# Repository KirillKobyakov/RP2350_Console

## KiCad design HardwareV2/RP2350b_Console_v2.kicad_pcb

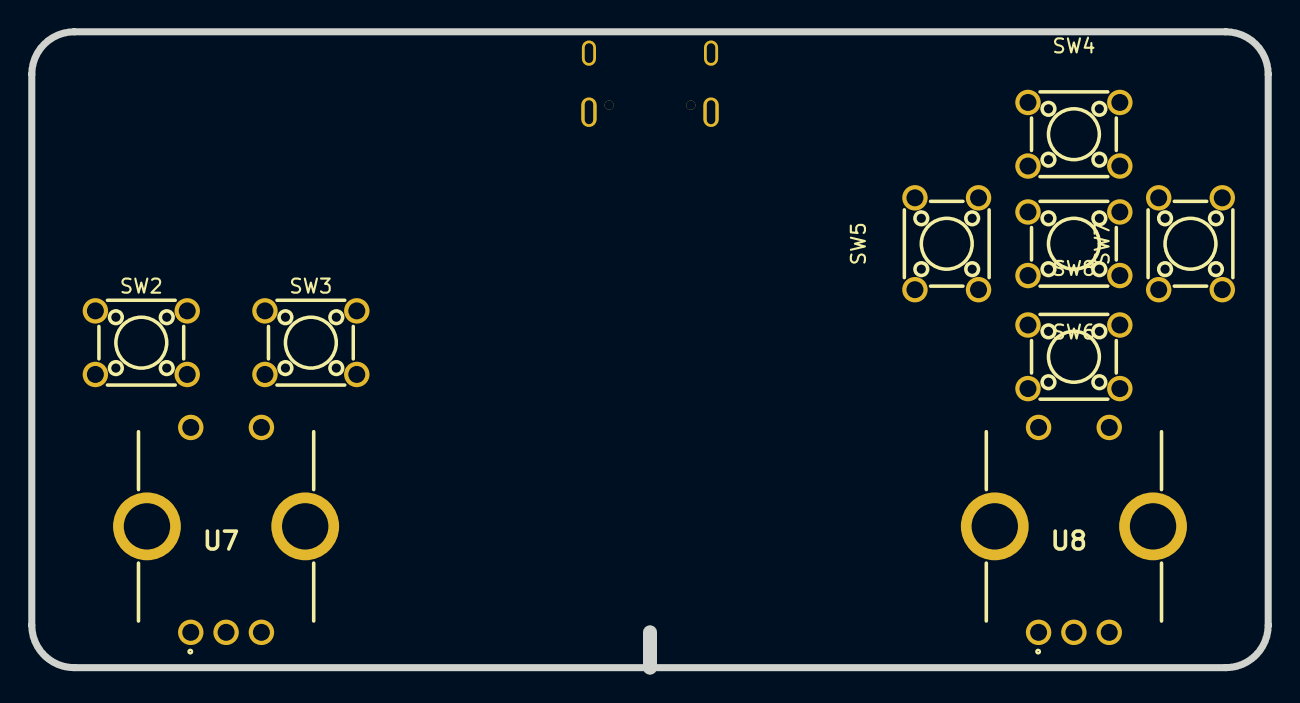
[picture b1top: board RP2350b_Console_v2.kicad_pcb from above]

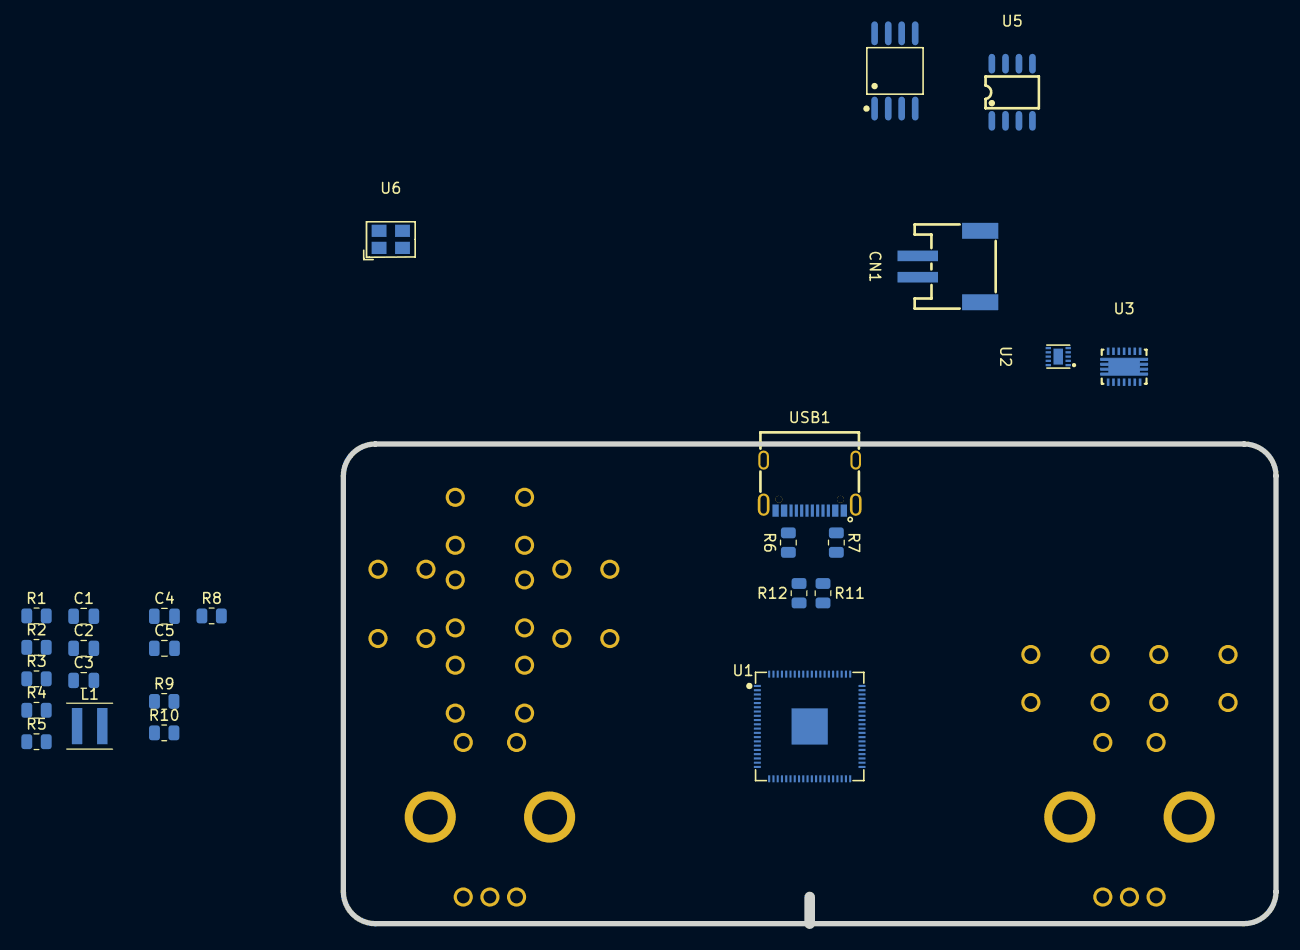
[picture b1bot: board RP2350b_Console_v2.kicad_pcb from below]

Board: 4 copper layers, 87.5 x 45.0 mm, 35 parts (26 on the bottom side), 26 nets, no tracks yet.

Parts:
C1: 47u; C_0805_2012Metric
C2: 22u; C_0805_2012Metric
C3: 100n; C_0805_2012Metric
C4, C5: 15p; C_0805_2012Metric
CN1: S2B-PH-SM4-TB(LF)(SN); CONN-SMD_P2.00_S2B-PH-SM4-TB-LF-SN
L1: 1.5u; L_Coilcraft_XxL4020
R1: 2k; R_0805_2012Metric
R2: 540; R_0805_2012Metric
R3: 10k; R_0805_2012Metric
R4, R5: R; R_0805_2012Metric
R6, R7: 5.1k; R_0805_2012Metric
R8, R9, R10: 1k; R_0805_2012Metric
R11, R12: 27; R_0805_2012Metric
SW2, SW3, SW4, SW5, SW6, SW7, SW8: 1825910-6; SW-TH_4P-L6.0-W6.0-P4.50-LS6.5
U1: RP2350B_C42415655; QFN-80_L10.0-W10.0-P0.40-TL-EP3.4
U2: BQ24040DSQR; WSON-10_L2.0-W2.0-P0.40-BL-EP
U3: TPS63021DSJR; VSON-14_L4.0-W3.0-P0.50-BL-EP_TI_DSJ
U4: W25Q128JVSIQTR; SOIC-8_L5.3-W5.3-P1.27-LS8.0-BL
U5: LY68L6400SLIT; SOP-8_L4.9-W3.9-P1.27-LS6.0-BL
U6: ABM8-272-T3; CRYSTAL-SMD_4P-L3.2-W2.5-BL-2
U7, U8: PEC12R-4215F-S0024; PEC12R-4XXXF-SXXXX_1
USB1: USB-310; USB-C-SMD_20P-P0.50-L7.4-W8.9

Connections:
+3V3: C1.1, U3.3 (FB), U3.4 (VOUT), U3.5 (VOUT), U4.8 (VCC), U5.8 (VCC)
+BATT: C2.1, CN1.1, R4.2, R5.2, U2.10 (OUT), U3.10 (VIN), U3.11 (VIN)
GND: C1.2, C2.2, C3.2, C4.2, C5.2, CN1.2, CN1.3, CN1.4, R1.2, R2.2, R3.2, R6.2, R7.2, SW2.3, SW2.4, SW3.3, SW3.4, U2.3 (VSS), U2.7 (ISET2), U2.11 (EP), U3.2 (GND), U3.13 (PS/SYNC), U3.15 (PGND), U4.4 (GND), U5.4 (VSS), U6.2 (GND), U6.4 (GND), USB1.0, USB1.A1 (GND), USB1.A12 (GND), USB1.B1 (GND), USB1.B12 (GND)
unnamed: C4.1, R8.1, U6.3
unnamed: L1.1, U3.8 (L1), U3.9 (L1)
unnamed: L1.2, U3.6 (L2), U3.7 (L2)
unnamed: R9.2, SW2.1, SW2.2
unnamed: R10.2, SW3.1, SW3.2
unnamed: C3.1, U3.1 (VINA)
unnamed: R11.2, U1.66 (USB_DM)
unnamed: R12.2, U1.67 (USB_DP)
unnamed: R2.1, U2.2 (ISET)
unnamed: R1.1, U2.4 (PRETERM)
unnamed: R3.1, U2.9 (TS)
unnamed: R6.1, USB1.A5 (CC1)
unnamed: R7.1, USB1.B5 (CC2)
QSPI_0: U1.72 (QSPI_SD0), U4.5 (DI), U5.5 (SI/SIO[0])
QSPI_1: U1.74 (QSPI_SD1), U4.2 (DO), U5.2 (SO/SIO[1])
QSPI_2: U1.73 (QSPI_SD2), U4.3 (IO2), U5.3 (SIO[2])
QSPI_3: U1.70 (QSPI_SD3), U4.7 (IO3), U5.7 (SIO[3])
QSPI_CLK: U1.71 (QSPI_SCLK), U4.6 (CLK), U5.6 (SCLK)
QSPI_SS0: R9.1, U1.75 (QSPI_SS), U4.1 (~CS)
USB_D+: R12.1, USB1.A6 (D+), USB1.B6 (D+)
USB_D-: R11.1, USB1.A7 (D-), USB1.B7 (D-)
VBUS: U2.1 (IN), USB1.A4 (VBUS), USB1.A9 (VBUS), USB1.B4 (VBUS), USB1.B9 (VBUS)
XIN: C5.1, U6.1

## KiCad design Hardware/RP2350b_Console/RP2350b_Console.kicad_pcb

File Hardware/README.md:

# RP2350_Console
A custom RP2350b console, which will include an LCD screen and rotary quad encoders. In this repository will include both hardware and software components for the design as well as assembly components and a tutorial.

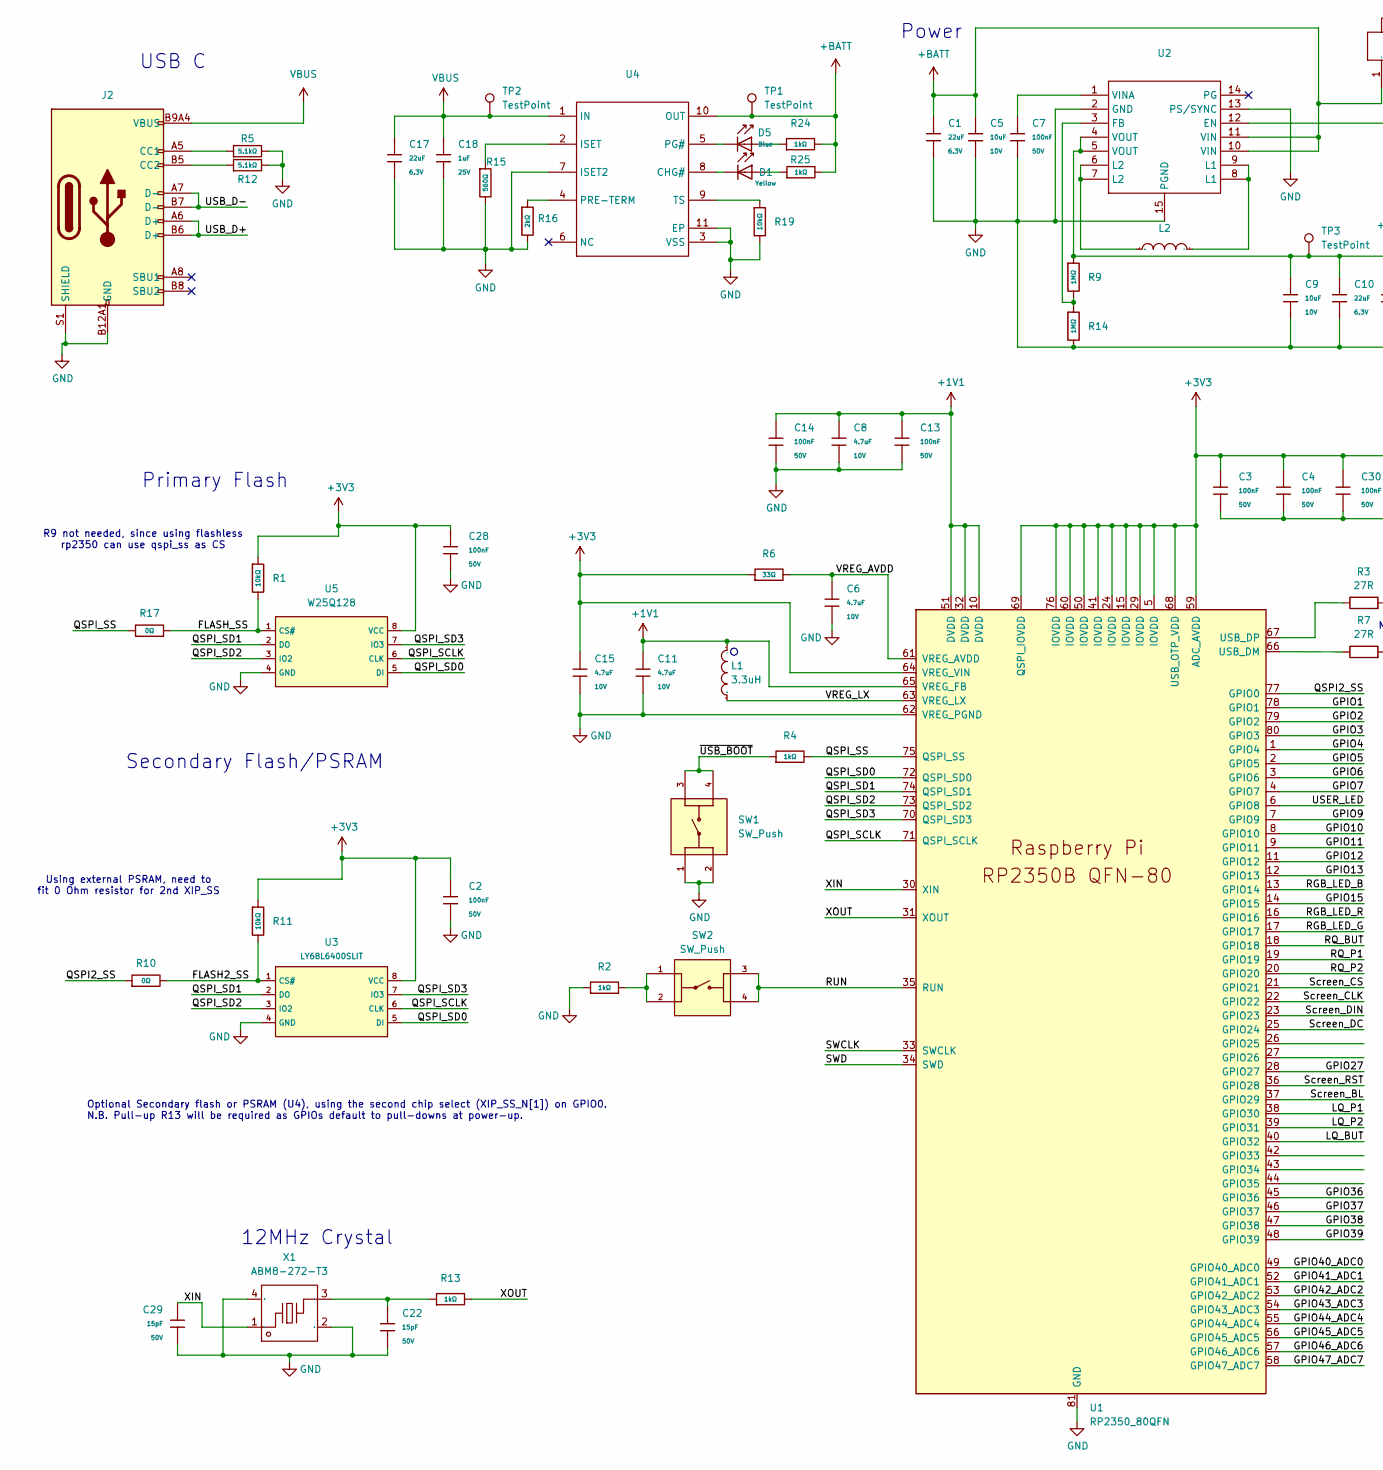
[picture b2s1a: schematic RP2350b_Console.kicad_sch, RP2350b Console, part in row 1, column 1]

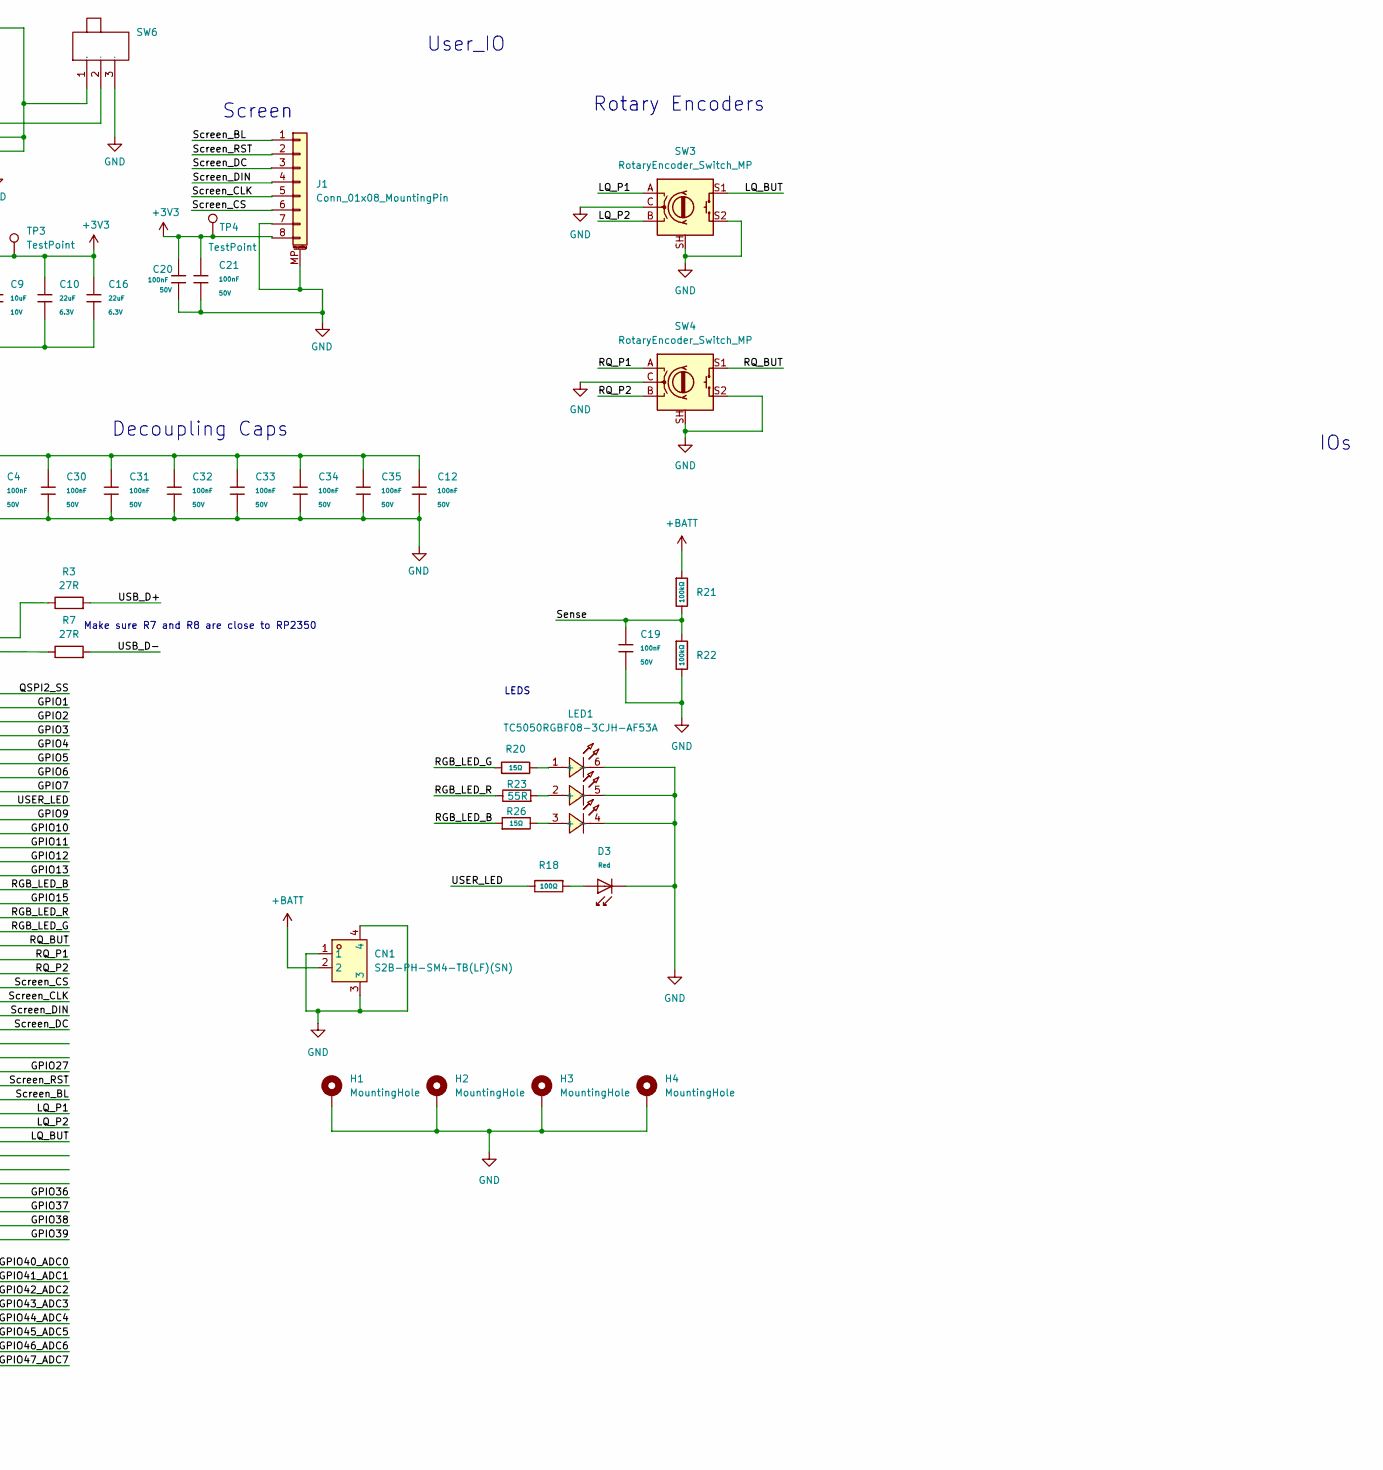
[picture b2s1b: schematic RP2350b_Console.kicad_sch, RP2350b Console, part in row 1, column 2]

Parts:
C1, C10, C16, C17: 22uF; C_0603; Voltage Rated 6.3V; Tolerance ±20%; Part CL10A226MQ8NRNC; LCSC C59461
C2, C3, C4, C7, C12, C13, C14, C19, C20, C21, C28, C30, C31, C32, C33, C34, C35: 100nF; C_0402; Voltage Rated 50V; Tolerance ±10%; Part CL05B104KB54PNC; LCSC C307331
C5, C9: 10uF; C_0603; Voltage Rated 10V; Tolerance ±10%; Part CL10A106KP8NNNC; LCSC C19702
C6, C8, C11, C15: 4.7uF; C_0402; Voltage Rated 10V; Tolerance ±20%; Part CL05A475MP5NRNC; LCSC C23733
C18: 1uF; C_0402; Voltage Rated 25V; Tolerance ±10%; Part CL05A105KA5NQNC; LCSC C52923
C22, C29: 15pF; C_0402; Voltage Rated 50V; Tolerance ±5%; Part 0402CG150J500NT; LCSC C1548
CN1: S2B-PH-SM4-TB(LF)(SN); CONN-SMD_P2.00_S2B-PH-SM4-TB-LF-SN; LCSC Part C295747
D1: Yellow; LED0603-R-RD_AMBER; Part KT-0603R; LCSC C2286
D3: Red; D_0603; Part KT-0603R; LCSC C2286
D5: Blue; LED0603-FD_BLUE; Part KT-0603R; LCSC C2286
H1, H2, H3, H4: MountingHole; MountingHole_2.2mm_M2_Pad_TopBottom
J1: Conn_01x08_MountingPin; Seeed 1.69 Inch LCD Module
J2: Connector, USB-TYPE-C-16P; TYPE-C-SMD_HX-TYPE-C-16PIN; LCSC C2927039
L1: 3.3uH; IND-SMD_L2.0-W1.6_AOTA-B201610S3R3-101-T; Manufacturer Part AOTA-B201610S3R3-101-T; LCSC Part Name AOTA-B201610S3R3-101-T
L2: 1.5uH; IND-SMD_L4.0-W4.0-A; Manufacturer Part XFL4020-152MEC; LCSC Part Name 1.5uH ±20%
LED1: TC5050RGBF08-3CJH-AF53A; LED-SMD_6P-L5.0-W5.0-TL_TC5050RGBF08; LCSC Part C784540
R1, R11, R19: 10kΩ; R_0402; Overload Voltage (Max) 50V; Tolerance ±1%; Part 0402WGF1002TCE; LCSC C25744
R2, R4, R13, R24, R25: 1kΩ; R_0402; Overload Voltage (Max) 50V; Tolerance ±1%; Part 0402WGF1001TCE; LCSC C11702
R3, R7: 27R; R0201
R5, R12: 5.1kΩ; R_0402; Overload Voltage (Max) 50V; Tolerance ±1%; Part 0402WGF5101TCE; LCSC C25905
R6: 33Ω; R_0402; Overload Voltage (Max) 50V; Tolerance ±1%; Part 0402WGF330JTCE; LCSC C25105
R9, R14: 1MΩ; R_0603; Overload Voltage (Max) 75V; Tolerance ±1%; Part 0603WAF1004T5E; LCSC C22935
R10, R17: 0Ω; R_0402; Overload Voltage (Max) 50V; Tolerance ±1%; Part 0402WGF0000TCE; LCSC C17168
R15: 560Ω; R_0603; Overload Voltage (Max) 75V; Tolerance ±1%; Part 0603WAF5600T5E; LCSC C23204
R16: 2kΩ; R_0402; Overload Voltage (Max) 50V; Tolerance ±1%; Part 0402WGF2001TCE; LCSC C4109
R18: 100Ω; R_0402; Overload Voltage (Max) 50V; Tolerance ±1%; Part 0402WGF1000TCE; LCSC C25076
R20, R26: 15Ω; R_0603; Overload Voltage (Max) 75V; Tolerance ±1%; Part 0603WAF150JT5E; LCSC C22810
R21, R22: 100kΩ; R_0603; Overload Voltage (Max) 75V; Tolerance ±1%; Part 0603WAF1003T5E; LCSC C25803
R23: 55R; R_0603
SW1, SW2: SW_Push; SW-TH_4P-L6.0-W6.0-P4.50-LS6.5; PARTREV C10
SW3, SW4: RotaryEncoder_Switch_MP; RotaryEncoder_Bourns_Vertical_PEC12R-3x17F-Sxxxx
SW6: SW-TH_MK-12D18-G040; Manufacturer Part MK-12D18-G040; LCSC Part Name 微型拨动开关
TP1, TP2, TP3, TP4: TestPoint; TestPoint_Pad_1.0x1.0mm
U1: RP2350_80QFN; RP2350-QFN-80-1EP_10x10_P0.4mm_EP3.4x3.4mm_ThermalVias
U2: VSON-14_L4.0-W3.0-P0.50-BL-EP_TI_DSJ; Manufacturer Part TPS63020DSJR; LCSC Part Name 高效率单电感升降压转换器
U3: LY68L6400SLIT; SOP-8_3.76x4.96mm_P1.27mm; LCSC C261881
U4: MSOP-10_L3.0-W3.0-P0.50-LS5.0-BL-EP; Manufacturer Part BQ24092DGQR; LCSC Part Name bq2409x 1A，单输入，单节锂离子和锂聚合物电池充电器
U5: W25Q128; SOIC-8_L5.3-W5.3-P1.27-LS8.0-BL; Part W25Q128JVSIQ; LCSC C97521
X1: ABM8-272-T3; CRYSTAL-SMD_4P-L3.2-W2.5-BL; Manufacturer Part ABM8-272-T3; LCSC Part Name ABM8-272-T3

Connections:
+1V1: C8.1, C11.1, C13.1, C14.1, L1.2, U1.10 (DVDD), U1.32 (DVDD), U1.51 (DVDD), U1.65 (VREG_FB)
+3V3: C2.1, C3.1, C4.1, C9.1, C10.1, C12.1, C15.1, C16.1, C20.1, C21.1, C28.1, C30.1, C31.1, C32.1, C33.1, C34.1, C35.1, J1.8, R1.1, R6.1, R9.1, R11.1, TP3.1, TP4.1, U1.5 (IOVDD), U1.15 (IOVDD), U1.24 (IOVDD), U1.29 (IOVDD), U1.41 (IOVDD), U1.50 (IOVDD), U1.59 (ADC_AVDD), U1.60 (IOVDD), U1.64 (VREG_VIN), U1.68 (USB_OTP_VDD), U1.69 (QSPI_IOVDD), U1.76 (IOVDD), U2.4 (VOUT), U2.5 (VOUT), U3.8 (VCC), U5.8 (VCC)
+BATT: C1.1, C5.1, CN1.2, R21.1, R24.2, R25.2, SW6.1, TP1.1, U2.10 (VIN), U2.11 (VIN), U4.10 (OUT)
/FLASH2_SS: R10.2, R11.2, U3.1 (CS#)
/FLASH_SS: R1.2, R17.2, U5.1 (CS#)
/GPIO1: U1.78 (GPIO1)
/GPIO2: U1.79 (GPIO2)
/GPIO3: U1.80 (GPIO3)
/GPIO4: U1.1 (GPIO4)
/GPIO5: U1.2 (GPIO5)
/GPIO6: U1.3 (GPIO6)
/GPIO7: U1.4 (GPIO7)
/GPIO9: U1.7 (GPIO9)
/GPIO10: U1.8 (GPIO10)
/GPIO11: U1.9 (GPIO11)
/GPIO12: U1.11 (GPIO12)
/GPIO13: U1.12 (GPIO13)
/GPIO15: U1.14 (GPIO15)
/GPIO27: U1.28 (GPIO27)
/GPIO36: U1.45 (GPIO36)
/GPIO37: U1.46 (GPIO37)
/GPIO38: U1.47 (GPIO38)
/GPIO39: U1.48 (GPIO39)
/GPIO40_ADC0: U1.49 (GPIO40_ADC0)
/GPIO41_ADC1: U1.52 (GPIO41_ADC1)
/GPIO42_ADC2: U1.53 (GPIO42_ADC2)
/GPIO43_ADC3: U1.54 (GPIO43_ADC3)
/GPIO44_ADC4: U1.55 (GPIO44_ADC4)
/GPIO45_ADC5: U1.56 (GPIO45_ADC5)
/GPIO46_ADC6: U1.57 (GPIO46_ADC6)
/GPIO47_ADC7: U1.58 (GPIO47_ADC7)
/LQ_BUT: SW3.S1, U1.40 (GPIO32)
/LQ_P1: SW3.A, U1.38 (GPIO30)
/LQ_P2: SW3.B, U1.39 (GPIO31)
/QSPI2_SS: R10.1, U1.77 (GPIO0)
/QSPI_SCLK: U1.71 (QSPI_SCLK), U3.6 (CLK), U5.6 (CLK)
/QSPI_SD0: U1.72 (QSPI_SD0), U3.5 (DI), U5.5 (DI)
/QSPI_SD1: U1.74 (QSPI_SD1), U3.2 (DO), U5.2 (DO)
/QSPI_SD2: U1.73 (QSPI_SD2), U3.3 (IO2), U5.3 (IO2)
/QSPI_SD3: U1.70 (QSPI_SD3), U3.7 (IO3), U5.7 (IO3)
/QSPI_SS: R4.2, R17.1, U1.75 (QSPI_SS)
/RGB_LED_B: R26.1, U1.13 (GPIO14)
/RGB_LED_G: R20.1, U1.17 (GPIO17)
/RGB_LED_R: R23.1, U1.16 (GPIO16)
/RQ_BUT: SW4.S1, U1.18 (GPIO18)
/RQ_P1: SW4.A, U1.19 (GPIO19)
/RQ_P2: SW4.B, U1.20 (GPIO20)
/RUN: SW2.3, SW2.4, U1.35 (RUN)
/SWCLK: U1.33 (SWCLK)
/SWD: U1.34 (SWD)
/Screen_BL: J1.1, U1.37 (GPIO29)
/Screen_CLK: J1.5, U1.22 (GPIO22)
/Screen_CS: J1.6, U1.21 (GPIO21)
/Screen_DC: J1.3, U1.25 (GPIO24)
/Screen_DIN: J1.4, U1.23 (GPIO23)
/Screen_RST: J1.2, U1.36 (GPIO28)
/Sense: C19.1, R21.2, R22.1
/USB_D+: J2.A6 (D+), J2.B6 (D+), R3.2
/USB_D-: J2.A7 (D-), J2.B7 (D-), R7.2
/USER_LED: R18.2, U1.6 (GPIO8)
/VREG_AVDD: C6.1, R6.2, U1.61 (VREG_AVDD)
/VREG_LX: L1.1, U1.63 (VREG_LX)
/XIN: C29.1, U1.30 (XIN), X1.1
/XOUT: R13.2, U1.31 (XOUT)
/~USB_BOOT: R4.1, SW1.3, SW1.4
GND: C1.2, C2.2, C3.2, C4.2, C5.2, C6.2, C7.2, C8.2, C9.2, C10.2, C11.2, C12.2, C13.2, C14.2, C15.2, C16.2, C17.2, C18.2, C19.2, C20.2, C21.2, C22.2, C28.2, C29.2, C30.2, C31.2, C32.2, C33.2, C34.2, C35.2, CN1.1, CN1.3, CN1.4, D3.1, H1.1, H2.1, H3.1, H4.1, J1.7, J1.MP (MountPin), J2.A12B1 (GND), J2.B12A1 (GND), J2.S1 (SHIELD), LED1.4 (-), LED1.5 (-), LED1.6 (-), R2.1, R5.2, R12.2, R14.2, R15.2, R16.2, R19.2, R22.2, SW1.1, SW1.2, SW3.C, SW3.S2, SW3.SH, SW4.C, SW4.S2, SW4.SH, SW6.3, U1.62 (VREG_PGND), U1.81 (GND), U2.2 (GND), U2.13 (PS/SYNC), U2.15 (PGND), U3.4 (GND), U4.3 (VSS), U4.7 (ISET2), U4.11 (EP), U5.4 (GND), X1.2 (GND), X1.4 (GND)
unnamed: C22.1, R13.1, X1.3
unnamed: D1.2, R25.1
unnamed: D3.2, R18.1
unnamed: D5.2, R24.1
unnamed: J2.A5 (CC1), R5.1
unnamed: J2.B5 (CC2), R12.1
unnamed: L2.1, U2.6 (L2), U2.7 (L2)
unnamed: L2.2, U2.8 (L1), U2.9 (L1)
unnamed: LED1.1 (+), R20.2
unnamed: LED1.2 (+), R23.2
unnamed: LED1.3 (+), R26.2
unnamed: R2.2, SW2.1, SW2.2
unnamed: R7.1, U1.66 (USB_DM)
unnamed: R3.1, U1.67 (USB_DP)
unnamed: SW6.2, U2.12 (EN)
unnamed: R9.2, R14.1, U2.3 (FB)
unnamed: C7.1, U2.1 (VINA)
unnamed: D1.1, U4.8 (CHG#)
unnamed: R15.1, U4.2 (ISET)
unnamed: D5.1, U4.5 (PG#)
unnamed: R16.1, U4.4 (PRE-TERM)
unnamed: R19.1, U4.9 (TS)
VBUS: C17.1, C18.1, J2.A9B4 (VBUS), J2.B9A4 (VBUS), TP2.1, U4.1 (IN)

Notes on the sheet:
Optional Secondary flash or PSRAM (U4), using the second chip select (XIP_SS_N[1]) on GPIO0. N.B. Pull-up R13 will be required as GPIOs default to pull-downs at power-up.
USB C
Decoupling Caps
IOs
Rotary Encoders
R9 not needed, since using flashless rp2350 can use qspi_ss as CS
12MHz Crystal
Primary Flash
LEDS
Make sure R7 and R8 are close to RP2350
Secondary Flash/PSRAM
Screen
User_IO
Power
Using external PSRAM, need to fit 0 Ohm resistor for 2nd XIP_SS

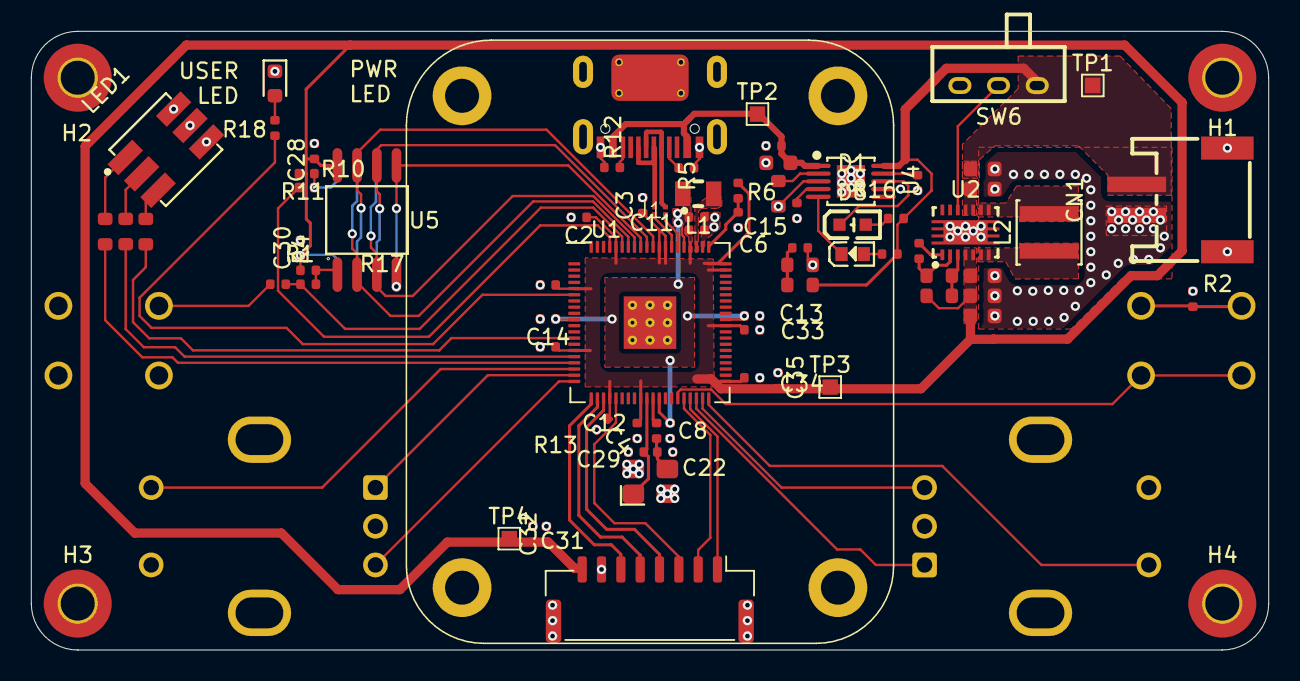
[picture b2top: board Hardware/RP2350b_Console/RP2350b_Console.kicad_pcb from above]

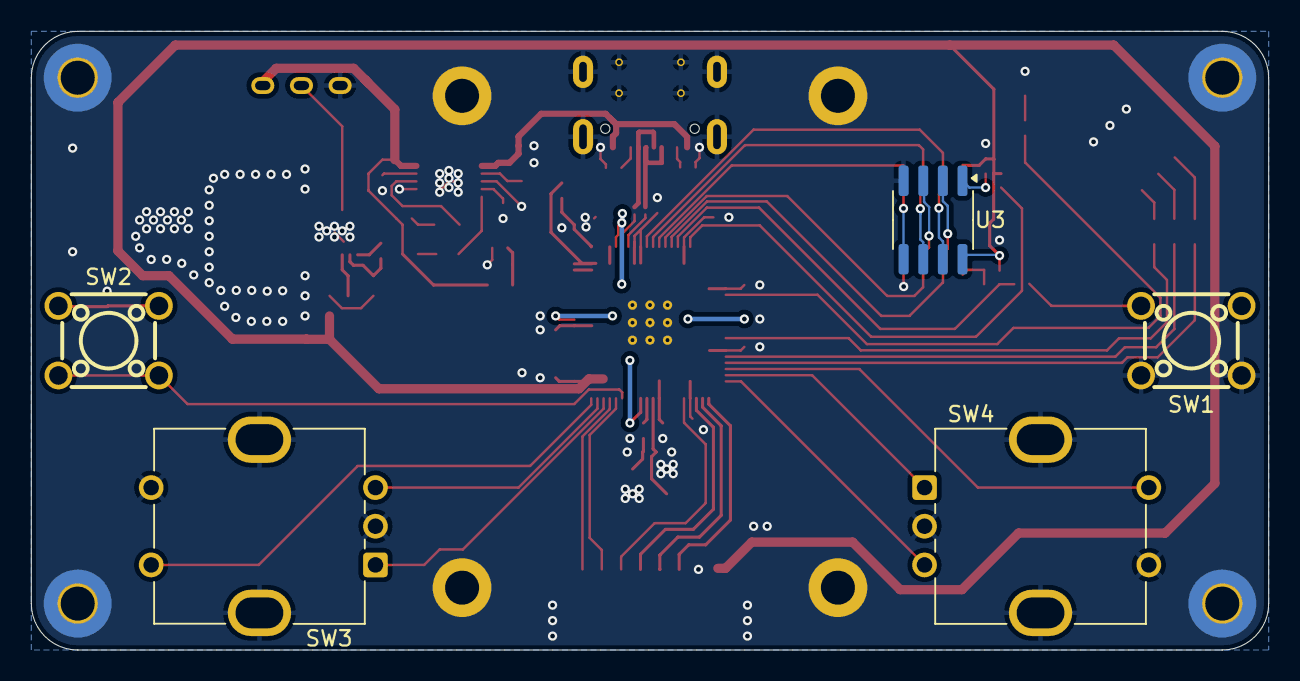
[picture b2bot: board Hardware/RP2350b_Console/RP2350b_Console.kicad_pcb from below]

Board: 2 copper layers, 80.0 x 40.0 mm, 83 parts (5 on the bottom side), 61 nets.

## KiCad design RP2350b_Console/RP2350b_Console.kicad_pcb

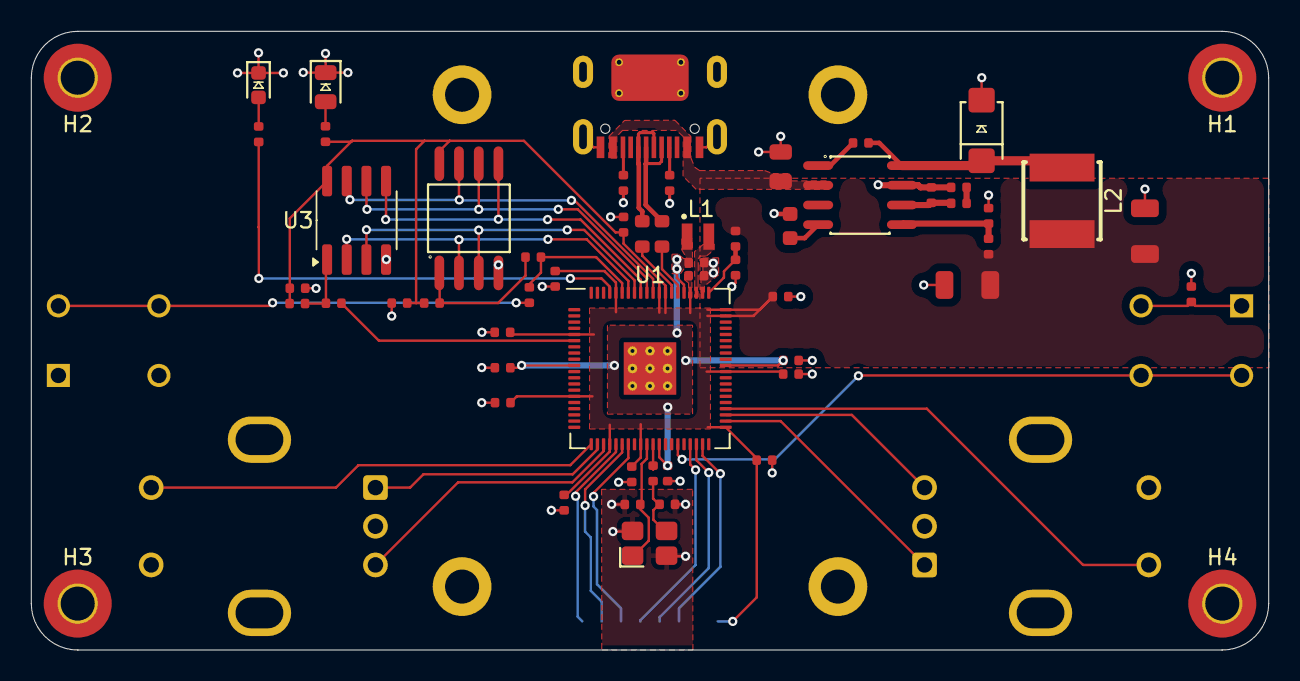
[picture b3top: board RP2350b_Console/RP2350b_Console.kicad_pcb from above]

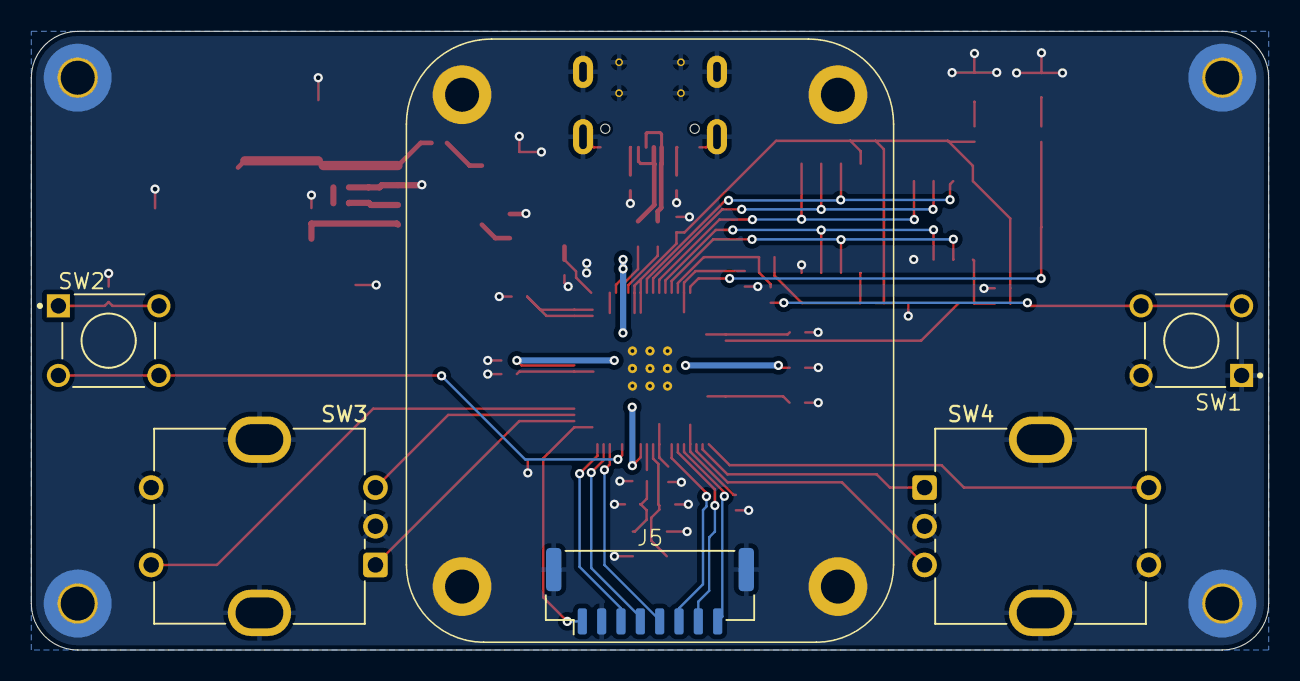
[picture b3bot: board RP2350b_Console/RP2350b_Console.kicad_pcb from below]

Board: 2 copper layers, 80.0 x 40.0 mm, 63 parts (5 on the bottom side), 48 nets.

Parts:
C1, C27: 100uF; C_1206
C2, C3, C4, C12, C13, C14, C23, C28, C30, C31, C32, C33, C34, C35: 100nF; C_0402
C5: 2.7nF; C_0603
C6, C8, C11, C15: 4.7uF; C_0402
C22, C29: 15pF; C_0402
C24: 1nF; C_0402
C25: 10pF; C_0402
C26: 22uF; C_0805
D1: SS24F; D_SMAF
D2: Green; D_0805
D3: Red; D_0603
H1, H2, H3, H4: MountingHole; MountingHole_2.2mm_M2_Pad_TopBottom
J2: Connector, USB-TYPE-C-16P; TYPE-C-SMD_HX-TYPE-C-16PIN
J5: Conn_01x08_MountingPin; Seeed 1.69 Inch LCD Module
L1: 3.3u; L_pol_2016
L2: 2.7uH; IND-SMD_L5.0-W5.0_FNR50XXS
R1, R11, R15: 10kΩ; R_0402
R2, R4, R13: 1kΩ; R_0402
R3, R7: 27Ω; R_0603
R5, R12: 5.1kΩ; R_0402
R6: 33Ω; R_0402
R8, R18: 100Ω; R_0402
R10, R17: 0Ω; R_0402
R14: 24kΩ; R_0402
R16: 3.3kΩ; R_0402
SW1, SW2: SW_Push; SW_1825910-6-4
SW3, SW4: RotaryEncoder_Switch_MP; RotaryEncoder_Bourns_Vertical_PEC12R-3x17F-Sxxxx
U1: RP2350_80QFN; RP2350-QFN-80-1EP_10x10_P0.4mm_EP3.4x3.4mm_ThermalVias
U2: TPS54331DR; SOIC-8_L5.0-W4.0-P1.27-LS6.0-BL
U3: LY68L6400SLIT; SOP-8_3.76x4.96mm_P1.27mm
U5: W25Q128; SOIC-8_L5.3-W5.3-P1.27-LS8.0-BL
X1: ABM8-272-T3; CRYSTAL-SMD_4P-L3.2-W2.5-BL

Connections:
+1V1: C8.1, C11.1, C13.1, C14.1, L1.1, U1.10 (DVDD), U1.32 (DVDD), U1.51 (DVDD), U1.65 (VREG_FB)
+3V3: C1.1, C2.1, C3.1, C4.1, C12.1, C15.1, C27.1, C28.1, C30.1, C31.1, C32.1, C33.1, C34.1, C35.1, J5.8, L2.2, R1.1, R6.1, R8.2, R11.1, R15.1, U1.5 (IOVDD), U1.15 (IOVDD), U1.24 (IOVDD), U1.29 (IOVDD), U1.41 (IOVDD), U1.50 (IOVDD), U1.59 (ADC_AVDD), U1.60 (IOVDD), U1.64 (VREG_VIN), U1.68 (USB_OTP_VDD), U1.69 (QSPI_IOVDD), U1.76 (IOVDD), U3.8 (VCC), U5.8 (VCC)
/FLASH2_SS: R10.2, R11.2, U3.1 (CS#)
/FLASH_SS: R1.2, R17.2, U5.1 (CS#)
/LQ_BUT: SW3.S1, U1.44 (GPIO35)
/LQ_P1: SW3.A, U1.42 (GPIO33)
/LQ_P2: SW3.B, U1.43 (GPIO34)
/QSPI2_SS: R10.1, U1.6 (GPIO8)
/QSPI_SCLK: U1.71 (QSPI_SCLK), U3.6 (CLK), U5.6 (CLK)
/QSPI_SD0: U1.72 (QSPI_SD0), U3.5 (DI), U5.5 (DI)
/QSPI_SD1: U1.74 (QSPI_SD1), U3.2 (DO), U5.2 (DO)
/QSPI_SD2: U1.73 (QSPI_SD2), U3.3 (IO2), U5.3 (IO2)
/QSPI_SD3: U1.70 (QSPI_SD3), U3.7 (IO3), U5.7 (IO3)
/QSPI_SS: R4.2, R17.1, U1.75 (QSPI_SS)
/RQ_BUT: SW4.S1, U1.21 (GPIO21)
/RQ_P1: SW4.A, U1.22 (GPIO22)
/RQ_P2: SW4.B, U1.23 (GPIO23)
/RUN: SW2.3, SW2.4, U1.35 (RUN)
/Screen_BL: J5.1, U1.25 (GPIO24)
/Screen_CLK: J5.5, U1.38 (GPIO30)
/Screen_CS: J5.4, U1.37 (GPIO29)
/Screen_DC: J5.3, U1.27 (GPIO26)
/Screen_DIN: J5.6, U1.39 (GPIO31)
/Screen_RST: J5.2, U1.26 (GPIO25)
/USB_D+: J2.A6 (D+), J2.B6 (D+), R7.2
/USB_D-: J2.A7 (D-), J2.B7 (D-), R3.2
/USER_LED: R18.2, U1.77 (GPIO0)
/VREG_AVDD: C6.1, R6.2, U1.61 (VREG_AVDD)
/VREG_LX: L1.2, U1.63 (VREG_LX)
/XIN: C29.1, U1.30 (XIN), X1.1
/XOUT: R13.2, U1.31 (XOUT)
/~USB_BOOT: R4.1, SW1.3, SW1.4
GND: C1.2, C2.2, C3.2, C4.2, C5.2, C6.2, C8.2, C11.2, C12.2, C13.2, C14.2, C15.2, C22.2, C24.2, C25.2, C26.2, C27.2, C28.2, C29.2, C30.2, C31.2, C32.2, C33.2, C34.2, C35.2, D1.2, D2.1, D3.1, H1.1, H2.1, H3.1, H4.1, J2.A12B1 (GND), J2.B12A1 (GND), J2.S1 (SHIELD), J5.7, J5.MP (MountPin), R2.1, R5.2, R12.2, R16.2, SW1.1, SW1.2, SW3.C, SW3.S2, SW3.SH, SW4.C, SW4.S2, SW4.SH, U1.62 (VREG_PGND), U1.81 (GND), U2.7 (GND), U3.4 (GND), U5.4 (GND), X1.2 (GND), X1.4 (GND)
unnamed: C22.1, R13.1, X1.3
unnamed: C24.1, R14.2
unnamed: D2.2, R8.1
unnamed: D3.2, R18.1
unnamed: J2.A5 (CC1), R5.1
unnamed: J2.B5 (CC2), R12.1
unnamed: R2.2, SW2.1, SW2.2
unnamed: R3.1, U1.66 (USB_DM)
unnamed: R7.1, U1.67 (USB_DP)
unnamed: C23.2, U2.1 (BOOT)
unnamed: C25.1, R14.1, U2.6 (COMP)
unnamed: C23.1, D1.1, L2.1, U2.8 (PH)
unnamed: C5.1, U2.4 (SS)
unnamed: R15.2, R16.1, U2.5 (VSENSE)
VBUS: C26.1, J2.A9B4 (VBUS), J2.B9A4 (VBUS), U2.2 (VIN)

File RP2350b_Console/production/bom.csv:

Designator,Footprint,Quantity,Value,LCSC Part #
"C1, C27",C_1206,2,100uF,C15008
"C11, C15, C6, C8",C_0402,4,4.7uF,C23733
"C12, C13, C14, C2, C23, C28, C3, C30, C31, C32, C33, C34, C35, C4",C_0402,14,100nF,C307331
"C22, C29",C_0402,2,15pF,C1548
C24,C_0402,1,1nF,C1523
C25,C_0402,1,10pF,C32949
C26,C_0805,1,22uF,C45783
C5,C_0603,1,2.7nF,C1609
D1,D_SMAF,1,SS24F,C18199202
D2,D_0805,1,Green,C2297
D3,D_0603,1,Red,C2286
J2,TYPE-C-SMD_HX-TYPE-C-16PIN,1,"Connector, USB-TYPE-C-16P",C2927039
J5,Seeed 1.69 Inch LCD Module,1,Conn_01x08_MountingPin,
L1,L_pol_2016,1,3.3u,
L2,IND-SMD_L5.0-W5.0_FNR50XXS,1,2.7uH,
"R1, R11, R15",R_0402,3,10kΩ,C25744
"R10, R17",R_0402,2,0Ω,C17168
"R12, R5",R_0402,2,5.1kΩ,C25905
"R13, R2, R4",R_0402,3,1kΩ,C11702
R14,R_0402,1,24kΩ,C25769
R16,R_0402,1,3.3kΩ,C25890
"R18, R8",R_0402,2,100Ω,C25076
"R3, R7",R_0603,2,27Ω,C25190
R6,R_0402,1,33Ω,C25105
"SW1, SW2",SW_1825910-6-4,2,SW_Push,
"SW3, SW4",RotaryEncoder_Bourns_Vertical_PEC12R-3x17F-Sxxxx,2,RotaryEncoder_Switch_MP,
U1,RP2350-QFN-80-1EP_10x10_P0.4mm_EP3.4x3.4mm_ThermalVias,1,RP2350_80QFN,
U2,SOIC-8_L5.0-W4.0-P1.27-LS6.0-BL,1,TPS54331DR,C9865
U3,SOP-8_3.76x4.96mm_P1.27mm,1,LY68L6400SLIT,C261881
U5,SOIC-8_L5.3-W5.3-P1.27-LS8.0-BL,1,W25Q128,C97521
X1,CRYSTAL-SMD_4P-L3.2-W2.5-BL,1,ABM8-272-T3,

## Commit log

2025-08-24 Initial KiCad project file
2025-08-28 first build
    first full build/hw design of the pcb. Changes to be made fr fr
2025-09-05 half way through second version
2025-09-05 removing lock files
2025-09-24 updates to project
2025-10-17 updates - build 1
2025-10-18 Restructuring repository
2025-10-31 software updates
2025-11-05 updates to pcb
2025-11-08 v2.0 design files
2025-12-26 hardware v2
2025-12-26 added updated battery and power schematic
2025-12-31 commiting before flight :), added in crystal and started doing the labels for the RP2350b
2026-01-21 updates pre routing
2026-04-26 initial v2 pcb layout minus passives
